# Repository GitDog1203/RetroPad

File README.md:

RetroPad

My 1st Hackpad!

Buttons: 

Up, Down, Left, Right, for movement

A, B, for selection

Other features:

Case to hold PCB

Screen for a small display.

Parts:

1x Seeed Xiao RP2040

6x MX-Style switches

1x 0.91 inch OLED display

4x M3x16mm screws

4x M3x5mx4mm heatset inserts

4x white blank DSA Keycaps

Screenshots:

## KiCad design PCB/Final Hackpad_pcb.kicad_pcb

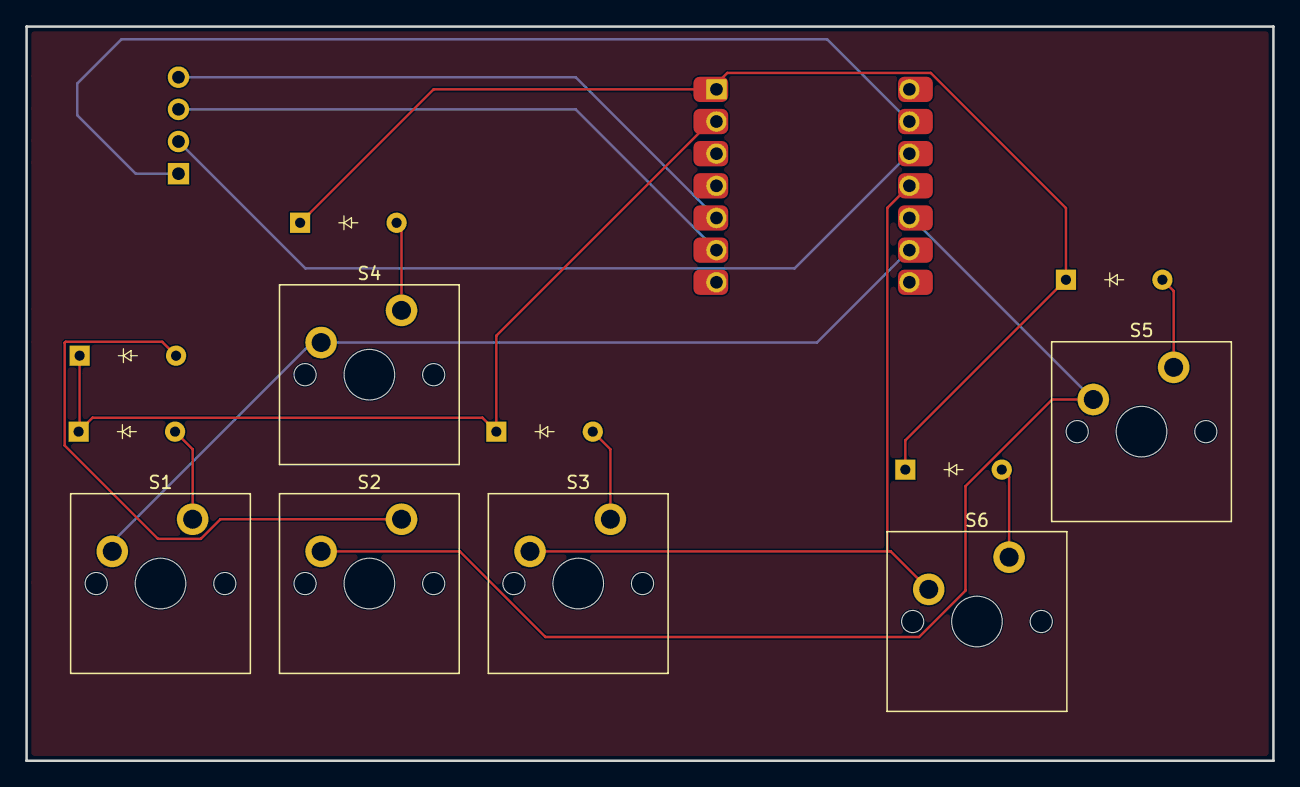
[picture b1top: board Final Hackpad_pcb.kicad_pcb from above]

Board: 2 copper layers, 98.5 x 58.0 mm, 14 parts (0 on the bottom side), 15 nets.

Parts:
D1, D2, D3, D4, D5, D6: Diode_DO-35
J1: OLED_128x32
S1, S2, S3, S4, S5, S6: MX_PCB_1.00u
U1: MOUDLE-SEEEDUINO-XIAO; Seeed_XIAO_RP2040

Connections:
+3.3V: J1.2 (VCC), U1.12 (3V3)
Column 0: S1.1, S4.1, U1.9 (PA7_A8_D8_SCK)
Column 1: S2.1, S5.1, U1.10 (PA5_A9_D9_MISO)
Column 2: S3.1, S6.1, U1.11 (PA6_A10_D10_MOSI)
GND: J1.1 (GND), U1.13 (GND)
unnamed: D1.2 (A), S1.2
unnamed: D2.2 (A), S2.2
unnamed: D3.2 (A), S3.2
unnamed: D4.2 (A), S4.2
unnamed: D5.2 (A), S5.2
unnamed: D6.2 (A), S6.2
Row 0: D1.1 (K), D2.1 (K), D3.1 (K), U1.2 (PA4_A1_D1)
Row 1: D4.1 (K), D5.1 (K), D6.1 (K), U1.1 (PA02_A0_D0)
SCL: J1.3 (SCL), U1.6 (PA9_A5_D5_SCL)
SDA: J1.4 (SDA), U1.5 (PA8_A4_D4_SDA)
